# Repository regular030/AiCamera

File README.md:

# SaturnAI Camera

**FPGA-based embedded vision camera with a custom ECP5 + ESP32-S3 PCBA, live
160x120 preview, and an FPGA-side orange-fruit detector.**

SaturnAI Camera is a custom hardware/software vision platform built around a
Lattice ECP5 FPGA, an OV-series DVP camera sensor, an ESP32-S3, and external
SDRAM. The current working path captures camera pixels on the FPGA, converts
YUYV to RGB565 in hardware, runs a small FPGA-side detector, sends a packed
parallel video stream to the ESP32-S3, and displays the result through a
localhost preview server.

Demo video: [SaturnAI Camera test video](https://youtu.be/1sOSSh_YdGI)

[Schematic PDF (October 24, 2026)](PCB/SCH_Schematic1_2026-10-24.pdf)
| [How I diagnosed the FPGA power short](Docs/FPGA_POWER_SHORT_DEBUG.md)
| [Project documentation](Docs/README.md)

> [!WARNING]
> The current PCB files are **not a manufacturing release**. Rev 1.0 is the
> repaired bring-up board. The updated schematic connects FPGA G9 to `+1V1`,
> but the PCB layout in the EasyEDA project still assigns G9 to `+3V3`.
> Complete the layout correction and the [Rev 1 errata](PCB/REV1_ERRATA.md)
> before fabrication. Please do **not** order the board from the current files.

> This repository is an active hardware bring-up repo. The top-level folders now
> point to the current working design; old reference projects and generated
> simulation outputs have been moved under `archive/`.

---

## Current Status

- Custom **ECP5 FPGA + ESP32-S3 camera PCBA** designed in EasyEDA.
- Current PCB revision is a bring-up board and should **not** be ordered as-is.
- FPGA power short repaired on the prototype; G9 corrected in the schematic.
  Propagating that correction into the PCB layout remains outstanding.
- FPGA DVP camera ingest is working at true **160x120** preview resolution.
- FPGA performs **YUYV to RGB565** conversion before the ESP32 receives pixels.
- FPGA transport uses **6 data lanes + strobe + frame gate**.
- RGB565 pixels are packed into **3 symbols per pixel** over the FPGA-to-ESP32 bus.
- ESP32-S3 forwards frames over USB/serial to a Python localhost preview server.
- FPGA-side orange-fruit detector uses an **8x6 grid of 20x20 tiles**.
- Latest timing-clean detector build used about **6.9k LUT4s**, **34 EBRs**, and
  **4 MULT18s**.
- Observed performance during bring-up was roughly **6.6 fps FPGA frame gate**
  and about **2 fps end-to-end preview**, mainly limited by ESP32 software GPIO
  capture and USB/serial transfer.
- SDRAM bring-up/test infrastructure exists at **120 MHz**, but the current live
  preview path does not require SDRAM framebuffering.

---

## How I Found The FPGA Power Short

My first clue was the ECP5 FPGA becoming extremely hot and appearing to burn.
I suspected a supply short to ground or another voltage rail, then found the
1.1 V and 3.3 V rails connected together. I recall about 3.38 V on the higher
rail and roughly 1.8 V on the core rail during the fault; these values are
approximate recollections.

The assembled boards showed the short while the bare PCBs did not. I checked
the FPGA pin assignments and found **G9, a VCC core-supply ball, accidentally
connected to 3.3 V instead of 1.1 V**. A technician added resin and disconnected
that ball so bring-up could continue. I have now corrected the schematic;
the routed PCB still needs the corresponding change.

The [full debugging writeup](Docs/FPGA_POWER_SHORT_DEBUG.md) records the
observations, reasoning, repair, and remaining checks.

---

## System Architecture

```mermaid
flowchart LR
  CAM["OV-series DVP camera"] -->|"PCLK / VSYNC / HREF / YUYV data"| FPGA["Lattice ECP5 FPGA"]
  FPGA -->|"YUYV -> RGB565, sync, detector, overlay"| PIPE["FPGA vision pipeline"]
  PIPE -->|"6 data lanes + strobe + frame gate"| ESP["ESP32-S3"]
  ESP -->|"USB/serial frame packets"| HOST["Python localhost preview"]
  FPGA -.->|"120 MHz test / future buffering"| SDRAM["External SDRAM"]
```

The split is intentional:

- **FPGA:** deterministic camera timing, pixel conversion, frame sync, detection,
  overlay, and video transport.
- **ESP32-S3:** GPIO capture bridge, USB/serial forwarding, debug/status packets,
  and future network/control tasks.
- **Host PC:** preview UI, logging, and training-data tooling.

---

## What Works Right Now

### FPGA Camera Pipeline

The active FPGA build is under:

```text
Lattice Diamond/recording/
```

Important current files:

- `fpga_top.v` - top-level camera/transport/detector design.
- `ov5640_sccb_init.v` - camera SCCB/I2C register bring-up sequence.
- `record.lpf` - Lattice pin constraints.
- `run_capture_clean_export_tasks.tcl` - Diamond build/export script.
- `model_box20_linear_plus_neg300/` - current learned tile-detector parameters.

The camera path is currently:

```text
DVP YUYV camera input
  -> FPGA byte/phase capture
  -> YUYV to RGB565 conversion
  -> 160x120 frame generation
  -> tile detector + overlay
  -> 6-lane packed GPIO transport
```

### ESP32-S3 Bridge

The active ESP-IDF firmware is under:

```text
ESP32/
```

Important current files:

- `ESP32/main/main.c` - ESP32 serial bridge and GPIO frame capture.
- `ESP32/main/wifi_profile.h.example` - local Wi-Fi profile template.
- `ESP32/main/idf_component.yml` - ESP-IDF component dependencies.

The current firmware receives the FPGA stream, packetizes frames with an
`AICAMF1` header, and sends them over USB/serial. Status packets use `AICAMS1`.

### Host Preview

The preview server is:

```text
scripts/serial_preview_server.py
```

It reads ESP32 serial packets, keeps the newest frame, and serves a live preview
at `http://127.0.0.1:8000/`.

---

## Repository Layout

```text
AiCamera/
|-- ESP32/                    ESP-IDF firmware for the ESP32-S3 bridge
|-- Lattice Diamond/recording/ Current FPGA RTL, constraints, and build scripts
|-- PCB/                      EasyEDA/Altium exports, PCB backups, datasheets
|-- Docs/                     Longer design notes and bring-up documentation
|-- scripts/                  Host preview/debug scripts
|-- sim/                      Verilator testbenches
|-- training/                 Training/model generation scripts
|-- ansys/, siwave/           SI/PI/EMI simulation project assets
|-- archive/                  Old reference projects, generated outputs, datasets
|-- README.md
|-- LICENSE
`-- .gitignore
```

### Archive Policy

The repo used to contain several temporary imported reference projects and
generated build folders at the top level. These are now grouped under:

```text
archive/legacy-code/     old reference SDRAM/HUB75/etc. code used during bring-up
archive/generated/       old Verilator outputs and waveform traces
archive/datasets/        historical captures and training data
```

The archive is kept for traceability, but new development should use the current
top-level source folders.

---

## Hardware / PCB

The PCB is a custom camera/FPGA carrier board. It is meant to put the complete
embedded-vision stack on one board instead of using loose dev modules and jumper
wires. The FPGA handles the real-time camera path, the ESP32-S3 handles host
communication/control, and the SDRAM is included for framebuffer and future
larger-pipeline work.

### Rev 1.0 Manufacturing Warning

Rev 1.0 is the board currently used for bring-up and the test video. It is
useful as proof that the architecture works, but it is **not** ready for someone
else to order unchanged.

- There is a known PCB/design issue in the current revision.
- The board files will be updated to match the bring-up fixes before this is
  treated as an orderable release.
- Do not send the current PCB files directly to fabrication/assembly unless you
  are intentionally reproducing the bring-up board.
- If you want to build one, please contact me first so I can share the latest
  status and corrected revision notes.

Known Rev 1.0 board issues are documented in
[`PCB/REV1_ERRATA.md`](PCB/REV1_ERRATA.md). In short: the bring-up boards needed
hardware repair around the FPGA power/BGA area, the microSD path is paused, the
ESP32-to-FPGA programming idea is not supported on this revision, and the ESP32
reset button path needs cleanup.

### What The PCB Includes

Main hardware blocks:

- **Lattice ECP5 FPGA** as the camera/vision datapath device.
- **ESP32-S3 module** for USB/serial, Wi-Fi-capable control, and host bridge
  firmware.
- **OV-series DVP camera connector** for the parallel camera sensor.
- **External SDRAM interface** for framebuffering and future higher-complexity
  image pipelines.
- **FPGA-to-ESP32 parallel GPIO video bus** with 6 data lanes, strobe, and frame
  gate.
- **Programming/debug access** for FPGA and ESP32 bring-up.
- Power regulation, decoupling, reset/boot support, status/debug routing, and
  board-level test access.

### What You Need To Build/Test One

This is not a polished kit yet, but a bring-up setup needs roughly:

- A fabricated/assembled SaturnAI Camera PCB/PCBA from the corrected revision.
- Lattice ECP5 FPGA matching the PCB footprint/BOM.
- ESP32-S3 module matching the PCB footprint/BOM.
- Compatible OV-series DVP camera module/sensor and matching flex/connector.
- External SDRAM part matching the PCB footprint/BOM.
- microSD card and matching socket/populated SD-card parts if you want to use
  the FPGA SD logging/write path.
- Regulators, passives, damping resistors, connectors, buttons, LEDs, and
  programming/debug headers from the board BOM.
- FTDI/FT232 or compatible FPGA programming adapter supported by
  `openFPGALoader`.
- USB cable for ESP32-S3 flashing and serial preview.
- A Windows machine with Lattice Diamond, ESP-IDF, Python, and MSYS2 tools.

Check the PCB project and BOM before buying parts. Some exact parts may change
for the next revision.

### Parts / Bring-Up Shopping Checklist

Do not treat this as a final BOM yet. It is a practical bring-up checklist for
the kind of hardware needed around the board:

| Item | Why it is needed |
| --- | --- |
| Corrected SaturnAI Camera PCB/PCBA | The custom board that connects the FPGA, ESP32-S3, camera, SDRAM, power, and debug interfaces. Do not order Rev 1.0 unchanged. |
| Lattice ECP5 FPGA | Runs deterministic camera capture, clock-domain crossing, RGB conversion, transport packing, overlay, and detector logic. |
| ESP32-S3 module | Handles USB/serial bridge firmware, Wi-Fi-capable control, debug/status reporting, and future web/control features. |
| OV-series DVP camera module | Provides the parallel PCLK/VSYNC/HREF/D[7:0] camera stream used by the FPGA. |
| Camera flex/connector/lens hardware | Needed to physically connect and focus the camera module. Exact mechanicals depend on the camera module used. |
| x16 SDRAM, such as W9825G6KH-class SDRAM | Provides external frame/line buffering capacity beyond the FPGA internal EBRs. |
| microSD card | Optional for SD logging experiments; useful if enabling the FPGA-side SD SPI writer path. |
| FTDI/FT232-style FPGA programmer | Used by `openFPGALoader` to flash/program the ECP5. |
| USB cable for ESP32-S3 | Used for ESP32 flashing, serial packets, and localhost preview. |
| Bench tools | Multimeter, soldering tools, hot air/rework if needed, and ideally an oscilloscope/logic analyzer for clocks, GPIO, and bring-up. |

### Design Rationale

| Design choice | Why it is in the design |
| --- | --- |
| **Lattice ECP5 FPGA** | The project needed real hardware video processing rather than MCU-only capture. The ECP5 gives enough LUTs, EBRs, IO, PLLs, and timing control for DVP ingest, CDC FIFOs, RGB conversion, frame packing, overlay, and small detector logic while staying cheaper and more accessible than jumping straight to a larger AMD/Xilinx device. |
| **OV-series 8-bit DVP camera instead of MIPI** | DVP is much easier to route, capture, and debug on a first FPGA camera board. PCLK, VSYNC, HREF, and D[7:0] are visible and deterministic. MIPI would require D-PHY/high-speed differential handling and a much harder FPGA receiver path. |
| **FPGA between camera and ESP32** | The ESP32 alone is not ideal for deterministic pixel capture at the target timing. The FPGA captures and cleans up pixels first, then sends the ESP32 a simpler reduced stream. |
| **External SDRAM** | FPGA internal memory is too small for full-frame buffering. SDRAM gives room for frame/line buffering, burst access, decoupling camera capture from transfer, and future higher-resolution or more complex pipelines. |
| **W9825G6KH-class x16 SDRAM** | x16 SDRAM offers useful bandwidth at lower complexity than DDR. It is a reasonable middle ground for frame buffering without making the first board much harder than necessary. |
| **Length-matched SDRAM/camera buses** | SDRAM and camera timing depend on skew between shared clock, control, address, and data nets. Matching improves timing margin and makes high-speed bring-up less random. |
| **ESP32-S3** | The FPGA handles real-time pixels; the ESP32 handles system glue: USB/serial, Wi-Fi-capable control, web/preview work, debugging, and future higher-level processing. |
| **Custom parallel FPGA-to-ESP32 video link** | UART/SPI-only transfer was too limiting for live preview. A parallel lane bus with strobe and frame gate gives the FPGA simple timing and gives the ESP32 more throughput than a basic serial control link. |
| **UART/control path** | UART remains useful for low-speed reliable control, mode changes, telemetry, debug prints, and bring-up even when the video bus is doing frame transfer. |
| **SCCB/I2C camera configuration** | OV sensors require register setup for resolution, pixel format, timing, JPEG/YUYV/RGB modes, and bring-up tuning. |
| **24 MHz camera clock** | The camera needs a stable external XCLK/MCLK. Providing a known clock makes the camera timing predictable and gives the FPGA design a stable capture target. |
| **CDC FIFOs / cross-clock handling** | Camera PCLK, FPGA system clock, SDRAM clock, and ESP32 transfer timing are different domains. CDC logic prevents metastability and frame corruption. |
| **YUYV/RGB565 bring-up path** | Raw color formats are easier to debug visually than jumping straight to JPEG or AI. They make frame sync, byte phase, color conversion, overlays, and transport bugs visible. |
| **JPEG experiments** | JPEG can reduce bandwidth dramatically for future streaming modes, but raw/YUYV/RGB565 was the better first path for bring-up and debugging. |
| **Tile/ROI FPGA acceleration** | The FPGA can cheaply compute tile features, motion/ROI masks, crops, and overlays in parallel before the ESP32 sees the frame. This reduces software load and makes the project closer to real edge-AI hardware. |
| **Series resistor footprints near drivers** | Optional 22-33 ohm damping gives bring-up flexibility for PCLK, camera data, SDRAM, and FPGA-to-ESP32 lines. Placing them near the driver helps control edge-rate/reflection behavior. |
| **Continuous ground/return-path control** | PCLK, SDRAM clock, DVP, and the FPGA-to-ESP32 bus need clean return paths. Poor return paths cause ringing, EMI, crosstalk, and timing bugs. |
| **Via stitching / fencing** | Stitching improves return-path continuity and helps contain fields around noisy/high-activity regions. This tied directly into the SIwave near-field improvements. |
| **Separate 1.1 V / 1.8 V / 3.3 V rails** | FPGA core, camera analog/IO, SDRAM/IO, and ESP32-side logic do not all run from one voltage. Separate rails and local decoupling are required for a stable board. |
| **Local decoupling around FPGA, SDRAM, camera, and ESP32** | Fast digital switching creates short current bursts. Local capacitors reduce rail droop and help keep the FPGA core, IO banks, SDRAM, and camera analog supplies stable. |
| **SIwave / IBIS / PDN simulation** | The board was checked as an electrical system, not just a routed PCB. Simulation work covered DC-IR, PDN behavior, near-field EMI, return paths, and high-speed interface integrity. |
| **JLCPCB-friendly design choices** | The board was designed to be manufacturable and affordable, with realistic parts/processes rather than an idealized board that would be hard to assemble or debug. |
| **JTAG, UART, test points, and debug access** | First revisions fail in interesting ways. Programming/debug access makes it possible to isolate whether an issue is FPGA logic, camera timing, SDRAM, ESP32 firmware, power, or routing. |
| **4-layer vs. higher-layer stackup tradeoff** | More layers make return paths, EMI, and PDN design easier. Fewer layers reduce cost and assembly friction. The project keeps that tradeoff explicit because the next revision may adjust the stackup around the SI/PI lessons from Rev 1.0. |

Short version: SaturnAI uses the ECP5 for deterministic pixel capture and
hardware preprocessing, DVP because it is FPGA-friendly and observable, SDRAM
because internal FPGA memory is too small for full frames, and the ESP32-S3 for
host control, serial/web preview, and system glue. The PCB was designed around
debuggability first: length matching, return-path control, damping footprints,
separate rails, test access, and simulation-backed SI/PI/EMI iteration.

### What Has Been Tested On Rev 1.0

- FPGA can be built and flashed through the Lattice/openFPGALoader flow.
- ESP32-S3 firmware can be built/flashed with ESP-IDF.
- Camera DVP capture path works well enough for true **160x120** live preview.
- FPGA-side **YUYV to RGB565** conversion is active.
- FPGA-to-ESP32 6-lane packed GPIO video transport works for live preview.
- ESP32-S3 can forward frames over USB/serial to the localhost preview server.
- FPGA-side tile detector can draw orange-fruit detection boxes in hardware.
- SDRAM 120 MHz test infrastructure exists, but full SDRAM framebuffer use is
  still part of bring-up/future work.

### PCB/SI/PI Work

Board-level design work included:

- FPGA bank power and IO planning.
- Camera, SDRAM, and ESP32 connector routing.
- Return-path planning and power-plane cleanup.
- Length matching where needed.
- 33 ohm series damping resistors on high-activity lines.
- Ansys SIwave/IBIS-based SI/PI/EMI review.

Earlier SIwave iterations reduced simulated near-field peaks from roughly
**15 kV/m to under 350 V/m** E-field and roughly **1000 A/m to under 7 A/m**
H-field through return-path cleanup, routing changes, damping, and power-plane
refinement.

---

## Software Requirements

### Required

- Windows 10/11
- Git
- Python 3.11 or newer
- `pyserial` for the host preview server
- ESP-IDF 5.5.x for ESP32-S3 firmware
- Lattice Diamond 3.14 for FPGA builds
- MSYS2 + `openFPGALoader` for FPGA programming

### Optional

- Verilator for RTL simulation
- Ansys SIwave for SI/PI/EMI project work

---

## Quick Start

### 1. Clone

```powershell
git clone https://github.com/regular030/AiCamera.git
cd AiCamera
```

### 2. Install Python Dependencies

```powershell
python -m pip install pyserial
```

### 3. Build and Flash the FPGA

Update paths if your Diamond/MSYS2 install is in a different location.

```powershell
& 'C:\lscc\diamond\3.14\bin\nt64\pnmainc.exe' `
  'C:\Users\User\Desktop\AiCamera\Lattice Diamond\recording\run_capture_clean_export_tasks.tcl'

& 'C:\msys64\ucrt64\bin\openFPGALoader.exe' `
  -c ft232 `
  'C:\Users\User\Desktop\AiCamera\Lattice Diamond\recording\_capture_clean_build\impl1\capclean_impl1.bit'
```

Known-good local bitstream path from the current workflow:

```text
Lattice Diamond/recording/_capture_clean_build/impl1/capclean_impl1.bit
```

### 4. Configure ESP32 Local Wi-Fi/Profile

If your firmware build expects a local profile, copy the example:

```powershell
Copy-Item ESP32\main\wifi_profile.h.example ESP32\main\wifi_profile.h
```

Then edit `ESP32/main/wifi_profile.h` for your local setup. This file is ignored
because it can contain private credentials.

### 5. Build and Flash the ESP32-S3

On this machine the working ESP-IDF Python environment is:

```text
C:\Users\User\.espressif\python_env\idf5.5_py3.11_env
```

Example PowerShell/cmd flow:

```powershell
$env:IDF_PYTHON_ENV_PATH = 'C:\Users\User\.espressif\python_env\idf5.5_py3.11_env'
cmd /c "C:\Users\User\esp\v5.5.1\export.bat && cd /d C:\Users\User\Desktop\AiCamera\ESP32 && idf.py -p COM3 build flash monitor"
```

Use the correct serial port for your board. During bring-up this board used
`COM3`.

### 6. Start the Local Preview

In another terminal:

```powershell
python scripts\serial_preview_server.py --port auto --baud 2000000 --http-port 8000
```

Open:

```text
http://127.0.0.1:8000/
```

---

## Frame Packet Format

The ESP32 sends frame packets with a 32-byte little-endian header:

```text
magic[8]       = "AICAMF1\0"
u16 width      = 160
u16 height     = 120
u16 format     = 0x0565 RGB565, 0x0444 RGB444 packed, or 0x0332 RGB332 packed
u16 header_len = 32
u32 frame_id
u32 payload_len
u32 capture_us
u32 gate_period_us
```

Status packets use:

```text
magic[8] = "AICAMS1\0"
```

The Python preview server handles RGB565, packed RGB444, and packed RGB332
payloads and converts them into a canvas preview.

---

## FPGA Detection Model

The current hardware detector is intentionally small enough to fit on the ECP5
while running inline with the frame pipeline.

Current detector shape:

- 160x120 frame
- 8x6 grid of 20x20 tiles
- RGB/orange feature accumulation per tile
- learned tile scoring
- neighborhood/grid filtering to reduce isolated false positives
- detection boxes drawn directly in FPGA hardware

This is not a full desktop-class CNN. It is a hardware-friendly detector built
for a small FPGA and live camera bring-up.

---

## SDRAM Notes

The board includes external SDRAM and a 120 MHz SDRAM test path. Current notes:

- 120 MHz SDRAM clock/test infrastructure exists.
- Address/data/control package-pin activity has been checked during bring-up.
- Full 16-bit SDRAM framebuffer use is still a bring-up target, not the required
  path for the current live preview.
- See `Lattice Diamond/recording/SDRAM_STRESS_TEST.md` for the latest SDRAM
  stress-test notes.

---

## Development Notes

- Keep generated build output out of commits.
- Keep private Wi-Fi credentials in `ESP32/main/wifi_profile.h`, not in Git.
- Use `archive/` for old experiments that are useful for reference but not part
  of the active design.
- If you add a new top-level tool or workflow, document it here or under `Docs/`.

---

## License

See `LICENSE`.

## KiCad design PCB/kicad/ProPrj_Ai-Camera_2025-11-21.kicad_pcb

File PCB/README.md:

# SaturnAI Camera PCB

This folder contains the board design assets for the SaturnAI Camera custom
ECP5 + ESP32-S3 camera PCBA.

## Manufacturing Warning

The current PCB files are **not an orderable release**.

Rev 1.0 is the repaired bring-up board used during development. In the October
24, 2026 update, the schematic connects FPGA G9 to `+1V1`, but the PCB layout
inside `Ai-Camera.eprj` still assigns G9 to `+3V3`. Propagate the schematic fix
into the layout and complete the remaining errata before fabrication or PCBA.

If you want to build this board, contact me first so I can share the latest
revision status, known issue, and corrected ordering notes.

See `REV1_ERRATA.md` before using the PCB files. The short version is that Rev
1.0 demonstrated the architecture, but it also had real bring-up issues: an
assembled-board FPGA power short that required repair, paused microSD bring-up,
an unsupported ESP32-to-FPGA programming path, and an ESP32 reset-button issue.

## What The Board Is

The PCB is a compact embedded-vision platform with:

- Lattice ECP5 FPGA for DVP camera ingest, RGB565 conversion, detector logic,
  frame synchronization, and video transport.
- ESP32-S3 module for USB/serial bridge firmware, host communication, and future
  Wi-Fi/control features.
- OV-series DVP camera connector.
- External SDRAM interface for framebuffer/future pipeline work.
- FPGA-to-ESP32 6-lane GPIO video bus with strobe and frame gate.
- FPGA/ESP32 programming and debug access.
- On-board regulation, decoupling, boot/reset support, and bring-up test access.

## What You Need

For a corrected future revision, a build needs:

- The SaturnAI Camera PCB/PCBA files for the fixed revision.
- BOM-matching Lattice ECP5 FPGA.
- BOM-matching ESP32-S3 module.
- Compatible OV-series 8-bit DVP camera module/sensor.
- Matching camera flex cable, connector, and lens/focus hardware.
- BOM-matching external SDRAM.
- microSD card and populated SD-card parts if you want to use the FPGA SD
  logging/write experiments. The current USB/serial live preview does not need
  the SD card.
- Regulators, passives, damping resistors, connectors, buttons, LEDs, and
  programming/debug headers.
- FTDI/FT232 or compatible FPGA programmer supported by `openFPGALoader`.
- USB cable for ESP32-S3 flashing and serial preview.
- Multimeter, soldering/rework tools, and ideally an oscilloscope or logic
  analyzer for clock, reset, SDRAM, camera, and GPIO bring-up.
- Lattice Diamond, ESP-IDF, Python, and MSYS2/openFPGALoader on the host.

Check the PCB project and BOM before buying parts. The next revision may change
exact camera connector details, damping resistor options, power cleanup, or
test-access placement.

## Why The Board Uses These Parts

| Design choice | Rationale |
| --- | --- |
| Lattice ECP5 FPGA | The camera path needs deterministic pixel timing and hardware parallelism. The ECP5 has enough LUTs, EBRs, IO, PLLs, and routing for DVP capture, RGB conversion, frame packing, SDRAM experiments, overlays, and detector logic without jumping to a much larger FPGA family. |
| OV-series DVP camera | An 8-bit DVP camera exposes PCLK, VSYNC, HREF, and D[7:0], which makes it easier to route, probe, and debug than MIPI D-PHY on a first custom FPGA camera board. |
| External x16 SDRAM | Internal FPGA EBRs are not large enough for full-frame buffering. SDRAM gives a practical path toward line/frame buffers, burst transfers, camera/host decoupling, and future higher-resolution modes. |
| ESP32-S3 | The FPGA handles timing-critical image work while the ESP32-S3 handles USB/serial, Wi-Fi-capable control, debug/status packets, and host-side preview/control firmware. |
| 6-lane FPGA-to-ESP32 video bus | UART and simple SPI were too limiting for live video. The custom lane/strobe/frame-gate link gives the FPGA a simple source-synchronous-style output and gives the ESP32 a faster raw capture path. |
| UART control path | UART is kept for reliable low-speed mode control, telemetry, debug prints, and bring-up even when video uses the parallel bus. |
| SCCB/I2C camera config | OV sensors need register programming for resolution, pixel format, timing, JPEG/YUYV/RGB modes, and bring-up tuning. |
| 24 MHz camera clock | The camera needs a stable XCLK/MCLK. Supplying a known clock gives predictable camera timing for the FPGA capture domain. |
| CDC buffering | Camera PCLK, FPGA system logic, SDRAM, and ESP32 transfer timing are separate domains. CDC logic is required to avoid metastability and frame corruption. |
| YUYV/RGB565 first | Raw visible color formats made frame sync, byte phase, transport, and overlay bugs easier to see before attempting heavier JPEG or AI flows. |
| Tile/ROI acceleration | The FPGA can compute simple tile features, ROI masks, and overlays in parallel, reducing what the ESP32 or host has to process. |
| Series damping footprints | Optional 22-33 ohm source-side resistors give bring-up flexibility for PCLK, camera data, SDRAM, and FPGA-to-ESP32 signals if ringing or EMI needs tuning. |
| Return-path control and stitching | PCLK, SDRAM clock, DVP, and the FPGA-to-ESP32 bus need clean return current paths. Stitching and fencing help reduce loop area, crosstalk, and near-field EMI. |
| Separate power rails and local decoupling | The FPGA, camera, SDRAM, and ESP32 need different rails and fast local current. Separate regulation and local capacitors keep digital switching from corrupting timing or analog camera behavior. |
| SIwave/IBIS/PDN workflow | The layout was treated as an electrical system: DC-IR, PDN behavior, return paths, near-field EMI, and high-speed interfaces were reviewed instead of only checking schematic connectivity. |
| Debug/programming access | JTAG, UART, test points, boot/reset access, and observable clocks make Rev 1.0 bring-up possible without guessing whether an issue is PCB, firmware, FPGA logic, or camera configuration. |

## Current Files

- [Ai-Camera.eprj](Ai-Camera.eprj) - updated EasyEDA project database; corrected
  G9 schematic, with the PCB layout correction still pending.
- [Schematic PDF](SCH_Schematic1_2026-10-24.pdf) - two-page export dated October
  24, 2026; page 1 is P1 and page 2 is FPGA. Page 2 shows G9 on `+1V1`.
- [REV1_ERRATA.md](REV1_ERRATA.md) - known Rev 1.0 hardware issues and required fixes.
- [FPGA power-short investigation](../Docs/FPGA_POWER_SHORT_DEBUG.md) - diagnosis,
  technician repair, evidence, and remaining verification.
- `Ai-Camera_backup/` - historical EasyEDA backups.
- `altium/` - historical February 2026 exports; not updated with the G9 correction.
- `Datasheets/` - local datasheets/pinout references used during layout.

## Bring-Up Status

Rev 1.0 has demonstrated the main camera/FPGA/ESP32 path:

- FPGA builds and flashes.
- ESP32-S3 builds and flashes.
- DVP camera capture works for true 160x120 preview.
- FPGA YUYV-to-RGB565 conversion works.
- FPGA-to-ESP32 packed GPIO video transport works.
- Serial localhost preview works.
- FPGA-side orange detector/overlay works.

Known remaining hardware/board work:

- Rev 1.0 has PCB/design issues that should be fixed before anyone orders the
  board. See `REV1_ERRATA.md`.
- SDRAM test infrastructure exists, but full SDRAM framebuffer use is still a
  bring-up/future-work item.

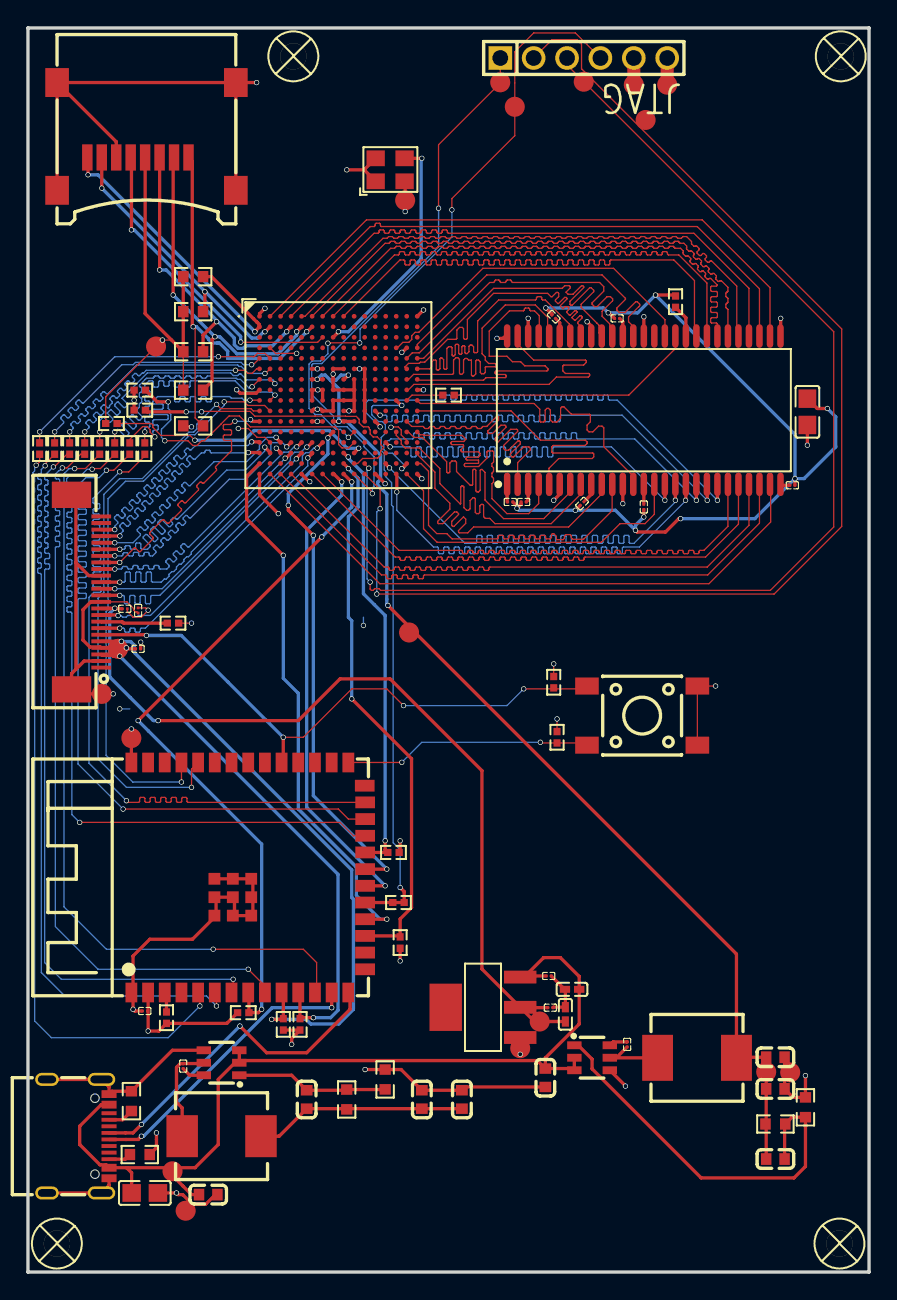
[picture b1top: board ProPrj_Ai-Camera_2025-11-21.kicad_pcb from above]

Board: 4 copper layers, 64.0 x 94.7 mm, 79 parts (0 on the bottom side), 122 nets.

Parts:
C8, C33: C0805
C10, C11, C12, C13, C14, C15, C16, C17, C18, C24, C29, C30, C34, C35, C36: C01005
C19, C20, C22, C23, C25, C26, C27, C28: C0603
C31, C32: C0402
CARD1: TF-SMD_DS1139-06-08SS4BSR
H1: HDR-TH_6P-P2.54-V-M-1
L1: IND-SMD_L7.0-W6.6
L2: IND-SMD_L7.3-W6.8
P1: FPC-SMD_AFC07-S24FCC-00
R1, R2, R3, R4, R5, R6, R7, R21, R22, R23, R24, R25, R26, R27, R28, R29, R30, R31, R32, R34, R35, R36, R37: R0402
R9, R10, R11, R12, R14, R15, R16, R17, R18, R19, R20: R0603
SCREW1, SCREW2, SCREW3, SCREW4: Screw-Hole-M2
U1: CABGA-256_L14.0-W14.0-R16-C16-P0.80-TL
U2: WIRELM-SMD_ESP32-S3-WROOM-1
U5: TSOP-54_L22.2-W10.2-P0.80-LS11.8-BL
U6, U7: SOT-23-6_L2.9-W1.6-P0.95-LS2.8-BR
U8: SOT-223-4_L6.5-W3.5-P2.30-LS7.0-BR
U9: OSC-SMD_4P-L3.2-W2.5-BL
U10: SW-SMD_4P-L6.0-W6.0-P4.50-LS9.2
USB1: USB-C-SMD_TYPE-C16PIN

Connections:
$1N8318: C15.2, U5.43
$1N8986: C16.2, U5.49
$1N9039: C14.1, U5.27
$1N9091: C13.1, U5.14
$1N9142: C12.1, U5.9
$1N9192: C11.1, U5.3
$1N9241: C10.1, U5.1
$1N9341: C8.1, C10.2, C11.2, C12.2, C13.2, C14.2, C15.1, C16.1, R1.2
$1N9437: R1.1, U5.37
$1N11348: R2.1, U5.38
$1N11975: R7.1, U2.3
$1N12553: R10.2, USB1.B5
$1N12557: R9.2, USB1.A5
$1N14416: C18.2, L1.1, U6.5
$1N14459: C18.1, U6.6
$1N14567: C19.1, R11.1, R12.2, U6.1
$1N14571: C19.2, C22.2, C23.2, L1.2, R11.2
$1N16832: C24.2, L2.1, U7.5
$1N16833: C24.1, U7.6
$1N16834: C25.1, R14.2, R15.1, U7.1
$1N17349: C29.2, C30.2, C31.1, C32.1
$1N24377: R23.2, U1.P10
$1N24422: R24.2, U1.N10
$1N24492: R25.2, U1.R10
$1N29790: R26.2, U2.5
$1N29833: R27.2, U2.6
$1N29916: R29.2, U2.9
$1N29959: R30.2, U2.12
$1N30002: R31.2, U2.23
$1N30085: R34.2, U2.25
$1N30089: R32.2, U2.24
$1N30093: R28.2, U2.7
$1N33205: P1.8, R35.1
+1V1: C25.2, C27.2, C28.2, L2.2, R15.2, U1.G6, U1.G7, U1.G9, U1.L8, U1.L9, U1.L10
+1V8: C29.1, C32.2, C36.1, P1.10, U8.2
+3V3: C8.2, C17.2, C34.1, C35.1, CARD1.4, H1.5, P1.4, P1.11, R3.1, R4.1, R5.2, R7.2, R16.2, R17.2, R18.2, R19.2, R20.2, R21.2, R22.2, R23.1, U1.F6, U1.F7, U1.F10, U1.F11, U1.G11, U1.H6, U1.H7, U1.H11, U1.J6, U1.J7, U1.J11, U1.K11, U1.L6, U1.L7, U1.L11, U2.2, U9.1, U9.4
+5V: C20.2, C26.2, C30.1, C31.2, C33.2, U6.2, U6.3, U7.2, U7.3, U8.3, USB1.A4B9, USB1.B4A9
CCLK: R6.1, R6.2, U1.J14, U2.19
CRYSTAL: U1.C8, U9.3
D0: R26.1, U1.E2
D1: R27.1, U1.E1
D2: R28.1, U1.F2
D3: R29.1, U1.F1
D4: R30.1, U1.G2
D5: R31.1, U1.G1
D6: R32.1, U1.J1
D7: R34.1, U1.J2
DIN: U1.T8, U2.20
DN: U2.13, USB1.A7
DONE: R3.2, U1.P9, U2.22
DOUT: U1.M8, U2.21
DP: U2.14, USB1.A6
GND: C17.1, C20.1, C22.1, C23.1, C26.1, C27.1, C28.1, C33.1, C34.2, C35.2, C36.2, CARD1.6, CARD1.9, CARD1.10, CARD1.11, CARD1.12, H1.6, P1.2, P1.15, P1.25, P1.26, R9.1, R10.1, R12.1, R14.1, R24.1, R25.1, R35.2, R36.2, R37.2, U1.A1, U1.A16, U1.D2, U1.D15, U1.F8, U1.F9, U1.G8, U1.G10, U1.H1, U1.H8, U1.H9, U1.H10, U1.H16, U1.J8, U1.J9, U1.J10, U1.K6, U1.K7, U1.K8, U1.K9, U1.K10, U1.N2, U1.N15, U1.T1, U1.T5, U1.T12, U1.T16, U2.1, U2.40, U2.41, U5.6, U5.12, U5.28, U5.41, U5.46, U5.52, U5.54, U6.4, U7.4, U8.1, U9.2, U10.2, U10.4, USB1.1, USB1.2, USB1.3, USB1.4, USB1.A1B12, USB1.B1A12
HREF: P1.9, U1.N7
INITN: R5.1, U1.T9, U2.8
MCLK: P1.13, U1.N6
M_CLK: CARD1.5, U1.C7
M_CMD: CARD1.3, R20.1, U1.B4
M_D0: CARD1.7, R18.1, U1.B2
M_D1: CARD1.8, R19.1, U1.B1
M_D2: CARD1.1, R16.1, U1.B6
M_D3: CARD1.2, R17.1, U1.B5
PCLK: P1.17, U1.L1
PROGRAM: R37.1, U2.27, U10.3
PROGRAMN: R4.2, U1.R9, U2.17
RESET: P1.6, R36.1, U2.31, U10.1
RX: U1.K1, U2.36
SCL: P1.5, R21.1, U2.10
SDA: P1.3, R22.1, U2.11
SD_A0: U1.T6, U5.23
SD_A1: U1.T4, U5.24
SD_A2: U1.T3, U5.25
SD_A3: U1.T2, U5.26
SD_A4: U1.A2, U5.29
SD_A5: U1.A3, U5.30
SD_A6: U1.A4, U5.31
SD_A7: U1.A5, U5.32
SD_A8: U1.A6, U5.33
SD_A9: U1.A7, U5.34
SD_A10: U1.T7, U5.22
SD_A11: U1.A8, U5.35
SD_A12: U1.A9, U5.36
SD_BA0: U1.K12, U5.20
SD_BA1: U1.L12, U5.21
SD_CAS_N: U1.R13, U5.17
SD_CLK: R2.2, U1.J15
SD_CS_N: U1.R15, U5.19
SD_DQ0: U1.L15, U5.2
SD_DQ1: U1.M16, U5.4
SD_DQ2: U1.K16, U5.5
SD_DQ3: U1.M15, U5.7
SD_DQ4: U1.M14, U5.8
SD_DQ5: U1.P16, U5.10
SD_DQ6: U1.R16, U5.11
SD_DQ7: U1.J16, U5.13
SD_DQ8: U1.D16, U5.42
SD_DQ9: U1.E15, U5.44
SD_DQ10: U1.E16, U5.45
SD_DQ11: U1.F15, U5.47
SD_DQ12: U1.F16, U5.48
SD_DQ13: U1.G15, U5.50
SD_DQ14: U1.G16, U5.51
SD_DQ15: U1.H15, U5.53
SD_DQM0: U1.T15, U5.15
SD_DQM1: U1.D14, U5.39
SD_RAS_N: U1.T14, U5.18
SD_WE_N: U1.N13, U5.16
SSPI_CS_N: U1.R1, U2.18
TCK: H1.1, U1.T10
TDI: H1.3, U1.R11
TDO: H1.4, U1.M10
TMS: H1.2, U1.T11
TX: U1.K2, U2.37
VSYNC: P1.7, U1.P6
Y2: P1.19, U1.P2
Y3: P1.21, U1.P1
Y4: P1.22, U1.N1
Y5: P1.20, U1.N3
Y6: P1.18, U1.N4
Y7: P1.16, U1.N5
Y8: P1.14, U1.P4
Y9: P1.12, U1.P5

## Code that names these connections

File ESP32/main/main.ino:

// esp32_fpga_ai_cam.ino
#include <SPI.h>

// ------------ Pins (adjust if needed) ------------
static const int PIN_FPGA_CS   = 5;   // SSPI_CS#
static const int PIN_SPI_MOSI  = 23;  // DIN -> FPGA DIN
static const int PIN_SPI_MISO  = 19;  // DOUT <- FPGA DOUT
static const int PIN_SPI_SCLK  = 18;  // CCLK

// ------------ SPI Commands ------------
#define CMD_READ_STATUS  0x00
#define CMD_READ_ROI     0x01
#define CMD_SET_MODE     0x02
#define CMD_STREAM_ROI   0x04

// status_b0 bits: [2]=recording, [1]=detect, [0]=roi_valid
struct RoiBox { uint16_t xmin, xmax, ymin, ymax; };

// ------------ TFLM placeholders ------------
extern const unsigned char g_model[];     // <-- put your TFLM model array here
extern const int g_model_len;
bool tflmInit();
int  tflmInferRGB565(const uint16_t* rgb565, int w, int h); // returns 0=none,1=person,2=car

SPISettings fpgaSPI(20*1000*1000, MSBFIRST, SPI_MODE0); // start at 20MHz; adjust as needed

void spiBegin() {
  SPI.begin(PIN_SPI_SCLK, PIN_SPI_MISO, PIN_SPI_MOSI, PIN_FPGA_CS);
  pinMode(PIN_FPGA_CS, OUTPUT);
  digitalWrite(PIN_FPGA_CS, HIGH);
}

void spiTxRx(const uint8_t* tx, uint8_t* rx, size_t n) {
  digitalWrite(PIN_FPGA_CS, LOW);
  for (size_t i=0;i<n;i++) {
    uint8_t out = tx ? tx[i] : 0x00;
    uint8_t in  = SPI.transfer(out);
    if (rx) rx[i] = in;
  }
  digitalWrite(PIN_FPGA_CS, HIGH);
}

uint8_t readStatus(uint8_t* b1 /*opt*/) {
  uint8_t tx[3] = { CMD_READ_STATUS, 0x00, 0x00 };
  uint8_t rx[3] = { 0 };
  SPI.beginTransaction(fpgaSPI);
  spiTxRx(tx, rx, 3);
  SPI.endTransaction();
  if (b1) *b1 = rx[2];
  return rx[1]; // status_b0
}

void setMode(uint8_t mode) {
  uint8_t tx[2] = { CMD_SET_MODE, (uint8_t)(mode & 0x03) };
  SPI.beginTransaction(fpgaSPI);
  spiTxRx(tx, nullptr, 2);
  SPI.endTransaction();
}

bool readROI(RoiBox& r) {
  uint8_t tx[9] = { CMD_READ_ROI,0,0,0,0,0,0,0,0 };
  uint8_t rx[9] = { 0 };
  SPI.beginTransaction(fpgaSPI);
  spiTxRx(tx, rx, 9);
  SPI.endTransaction();
  // order: xmin_lo, xmin_hi, xmax_lo, xmax_hi, ymin_lo, ymin_hi, ymax_lo, ymax_hi
  r.xmin = rx[1] | ((rx[2] & 0x0F) << 8);
  r.xmax = rx[3] | ((rx[4] & 0.0F) << 8);
  r.ymin = rx[5] | ((rx[6] & 0x0F) << 8);
  r.ymax = rx[7] | ((rx[8] & 0x0F) << 8);
  return true;
}

// STREAM_ROI: header= 0xAA, w_hi, w_lo, h_hi, h_lo (lo nybbles are padded <<4)
// Then w*h*2 bytes of RGB565
bool streamROI_andReadRGB565(std::unique_ptr<uint16_t[]>& outBuf, int& W, int& H) {
  SPI.beginTransaction(fpgaSPI);
  // send just the command byte; then keep clocking to read bytes out
  digitalWrite(PIN_FPGA_CS, LOW);
  SPI.transfer(CMD_STREAM_ROI);

  // read 5 header bytes
  uint8_t h[5];
  for (int i=0;i<5;i++) h[i] = SPI.transfer(0x00);

  if (h[0] != 0xAA) { digitalWrite(PIN_FPGA_CS,HIGH); SPI.endTransaction(); return false; }
  W = ( (int)h[1]<<4 ) | ( (h[2]>>4) & 0x0F );
  H = ( (int)h[3]<<4 ) | ( (h[4]>>4) & 0x0F );
  if (W==0 || H==0)   { digitalWrite(PIN_FPGA_CS,HIGH); SPI.endTransaction(); return false; }

  size_t pixCount = (size_t)W * (size_t)H;
  size_t bytes    = pixCount * 2;
  outBuf.reset(new uint16_t[pixCount]);

  // read pixels
  for (size_t i=0;i<pixCount;i++) {
    uint8_t hi = SPI.transfer(0x00);
    uint8_t lo = SPI.transfer(0x00);
    outBuf[i] = (uint16_t(hi)<<8) | lo;
  }

  digitalWrite(PIN_FPGA_CS, HIGH);
  SPI.endTransaction();
  return true;
}

// --- Minimal demo: poll and classify ---
void setup() {
  Serial.begin(115200);
  spiBegin();
  delay(50);
  setMode(2); // 2 = record+detect

  // tflmInit() should set up TensorArena, resolver, interpreter using g_model[]
  if (!tflmInit()) {
    Serial.println("TFLM init failed (placeholder). Add your model array.");
  }
}

void loop() {
  // 1) wait for ROI
  uint8_t s0, s1;
  for (;;) {
    s0 = readStatus(&s1);
    bool roi_valid = (s0 & 0x01);
    if (roi_valid) break;
    delay(10);
  }

  // 2) read ROI box (optional, for logging)
  RoiBox r; readROI(r);
  Serial.printf("ROI: x[%u..%u] y[%u..%u]\n", r.xmin, r.xmax, r.ymin, r.ymax);

  // 3) stream ROI pixels (RGB565)
  std::unique_ptr<uint16_t[]> rgb565;
  int W=0,H=0;
  if (!streamROI_andReadRGB565(rgb565, W, H)) {
    Serial.println("Stream failed");
    delay(50);
    return;
  }
  Serial.printf("Got ROI %dx%d\n", W, H);

  // 4) Run inference (convert inside tflmInferRGB565 if needed)
  int label = tflmInferRGB565(rgb565.get(), W, H);
  if (label == 1) Serial.println("DETECT: PERSON");
  else if (label == 2) Serial.println("DETECT: CAR");
  else Serial.println("DETECT: NONE");

  delay(50);
}

// ====== --- TFL-Micro stubs you’ll fill with your model --- ======
#include "tensorflow/lite/micro/all_ops_resolver.h"
#include "tensorflow/lite/micro/micro_interpreter.h"
#include "tensorflow/lite/schema/schema_generated.h"

namespace {
  tflite::MicroMutableOpResolver<8> resolver;
  constexpr int kArenaSize = 200*1024; // tune as needed
  static uint8_t tensor_arena[kArenaSize];
  const tflite::Model* model = nullptr;
  std::unique_ptr<tflite::MicroInterpreter> interpreter;
  TfLiteTensor* input_tensor = nullptr;
}

bool tflmInit() {
  // Register ops you need (Conv2D, DepthwiseConv2D, Add, Mul, MaxPool, Reshape, FullyConnected, Softmax, etc.)
  resolver.AddConv2D();
  resolver.AddDepthwiseConv2D();
  resolver.AddRelu();
  resolver.AddMaxPool2D();
  resolver.AddFullyConnected();
  resolver.AddReshape();
  resolver.AddSoftmax();

  model = tflite::GetModel(g_model);
  if (model->version() != TFLITE_SCHEMA_VERSION) return false;
  interpreter.reset(new tflite::MicroInterpreter(model, resolver, tensor_arena, kArenaSize));
  if (!interpreter) return false;
  if (interpreter->AllocateTensors() != kTfLiteOk) return false;
  input_tensor = interpreter->input(0);
  return (input_tensor != nullptr);
}

// Resize & normalize RGB565 -> model input, then invoke.
// Return 1=person, 2=car, 0=none.
int tflmInferRGB565(const uint16_t* rgb565, int W, int H) {
  if (!input_tensor) return 0;
  // Example assumes model input is 96x96x3 uint8
  const int in_w = 96, in_h = 96;
  if ((input_tensor->dims->data[1] != in_h) ||
      (input_tensor->dims->data[2] != in_w) ||
      (input_tensor->dims->data[3] != 3)) {
    return 0;
  }

  uint8_t* in = input_tensor->data.uint8;

  // Nearest-neighbor resize RGB565 -> RGB888 (or keep RGB565 and unpack)
  for (int y=0; y<in_h; ++y) {
    int sy = (y * H) / in_h;
    for (int x=0; x<in_w; ++x) {
      int sx = (x * W) / in_w;
      uint16_t p = rgb565[sy*W + sx];
      uint8_t R = (p >> 11) & 0x1F;
      uint8_t G = (p >> 5)  & 0x3F;
      uint8_t B = (p >> 0)  & 0x1F;
      // expand to 8-bit
      uint8_t r8 = (R << 3) | (R >> 2);
      uint8_t g8 = (G << 2) | (G >> 4);
      uint8_t b8 = (B << 3) | (B >> 2);
      *in++ = r8; *in++ = g8; *in++ = b8;
    }
  }

  if (interpreter->Invoke() != kTfLiteOk) return 0;

  // Assume output is 3-class logits [none, person, car] — adjust to your model
  TfLiteTensor* out = interpreter->output(0);
  int best = 0; float bestv = -1e9;
  for (int i=0;i<out->dims->data[out->dims->size-1]; ++i) {
    float v = (out->type==kTfLiteFloat32) ? out->data.f[i] : out->data.uint8[i];
    if (v > bestv) { bestv = v; best = i; }
  }
  // Map indices to our labels
  if (best==1) return 1; // person
  if (best==2) return 2; // car
  return 0;              // none
}

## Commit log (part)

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2026-01-20 updated alt and pcb
2026-01-27 updated pcb
2026-01-28 made the decupling caps better
2026-01-28 improved heat loss, moved camera to bank 1, changed bank one to 1.8V, updated lattice diamond
2026-01-28 export ansys EDB
2026-01-29 added more heat protection, added 2v5 (inc buck) for FPGA, added programing usb c, so now there are 2 usbcs
2026-01-29 added 2v5 for camera, more thermal reliefs
2026-02-02 put all of the power rails in inner 2
2026-02-03 brang 5V to inner2, 1v1 is now fully in inner 2 instead of being mixed, improved DC IR
2026-02-03 forgot to check DRC (oops)
2026-02-04 Made 5v and 1v1 bigger traces and multple contact points, hopefull Voltage loss is fixed, last time 1v1 showed as 1v 💀
2026-02-04 siwave doesnt like teardrops, so removed it
2026-02-04 brang 1v1 closer to FPGA, added pour to 5v
2026-02-04 added more vias on the power rails to help with voltage, increased 1v1 cap trace width, decreased 5v fill (covered 3v3), added more support for 3v3, fixed path length for SDRAM (old kb was not it)
2026-02-04 First siwave commit, DC IR passed (within my standards)
2026-02-04 removed old code from lattice, added IBS files, improved a hotspot on the PCB
2026-02-05 fixed IBIS
2026-02-05 added Rs to SDRAM to help with ringing
2026-02-05 updated crystal from 1A to 0.05A, LOTS of ringing near receivers
2026-02-05 maybe fixed ringing (80% not :P)
2026-02-05 hopefully fixed ringing on A, and address pins
2026-02-06 improved hotspot near ESP32
2026-02-06 SDRAM
2026-02-06 added sdcard to lattice diamond (updated IBIS)
2026-02-07 added series Rs to camera
2026-02-07 moved CCLK, updated IBIS for FPGA, added Rs to ESP32 SPI pins
2026-02-24 moved esp32 3v3 vias a bit further, added more vias for 3v3, decreased gnd vias near 3v3 rails
2026-02-25 added gnds vias near hotspot (yeah removing the gnd vias was not the play :pensive:)
2026-02-26 increased track width, reverted past changes, removed lots of gnd vias, rerouted major power lines
2026-02-27 converted PCB to 6 layers for better EMI
2026-02-27 reduced hotspots, added more decaps near usbc
2026-02-27 siwave update
2026-02-27 added more gnd vias to help with E field, H field has passed
2026-02-28 added gnd vias around the PCB to help with E field
2026-02-28 more gnd vias for E field
2026-02-28 added more GND vias near top right
2026-02-28 drc issue in last commit
2026-02-28 fixed drc (hopefully)
2026-02-28 more gnd vias HAHAHHAHAAHAHAH
2026-03-01 added finishing touches, might be final (hopefully)
2026-03-01 Near field passes, H field good til 5GHz, E field good til 4 GHz
2026-03-01 all tests passed, ready to manufacture
2026-03-02 pcb ordered
2026-03-04 Revise README with project overview and status
    Expanded README to detail project goals, architecture, design choices, and current status.
2026-03-04 Create LICENSE
2026-03-06 CNN done, VGA @ around 20fps works and compiles, using verilator to test files, will update readme with more info soon
2026-03-06 UART verified - verilator
2026-03-12 big commit, finshed verilog code, finshed esp32 code, verilator and lattice dmd tests pased, readmes and docs will need to be updated
2026-03-18 added ESP32 to FPGA programmer
2026-04-09 esp32 stuff, update soon :P
2026-05-12 image detection works!!!!! more info coming soon
2026-05-15 sdram is better, just updating verilog more, repo still being worked on
2026-05-19 V1.0 done
2026-05-19 Revise and reorganize docs for SaturnAI Camera
    Large documentation overhaul to reflect the cleaned/active SaturnAI Camera repo and bring-up lessons. Updated guides to clarify the active FPGA/ESP32 workflows, protocol formats, build/flash examples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

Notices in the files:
README.md:
See `LICENSE`.
